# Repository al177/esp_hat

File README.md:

Attributions:
http://github.com/mcuos/kicad-lib - various footprints
https://github.com/StefanHamminga/SH_Antennas.pretty - antenna

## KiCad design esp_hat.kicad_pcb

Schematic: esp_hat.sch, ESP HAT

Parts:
ANT1: ANT_INVERTED_F; TI_DN007_2.4GHz
C1, C2: 10pF; 0603(1608m)-CHIP-CAP
C3: 5.6pF; 0603(1608m)-CHIP-CAP
C4, C5: 0.1uF; 0603(1608m)-CHIP-CAP
C6, C7: 10uF; 0603(1608m)-CHIP-CAP
FB1: FILTER; 0603(1608m)
J1: U.FL; U.FL-COAX
L1, L2: DNP; 0603(1608m)
P1: CONN_02X20; Socket_Strip_Straight_2x20_pi
P2: CONN_01X03; GS3
R1: DNP; 0603(1608m)-CHIP-RESISTOR
R2: 0; 0603(1608m)-CHIP-RESISTOR
R3, R4, R5: DNP; GS2
R6: 12.0K; 0603(1608m)-CHIP-RESISTOR
R7, R8, R9, R10, R11, R12: 200; 0603(1608m)-CHIP-RESISTOR
U1: ESP8266EX; QFN-32-1EP_5x5mm_Pitch0.5mm
U2: AP1117D33; SOT-223-REG_VOUTSLUG
W1: RXD; Measurement_Point_Round-SMD-Pad_Small
W2: TXD; Measurement_Point_Round-SMD-Pad_Small
W3, W4, W5, W6: MOUNT; NPTH_Hole_2_75mm
Y1: 26MHz; crystal_FA238-TSX3225

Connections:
+3V3: C4.1, C5.1, C7.1, U1.1 (VDDA), U1.3 (VDD3P3), U1.4 (VDD3P3), U1.11 (VDDPST), U1.17 (VDDPST), U1.29 (VDDD), U1.30 (VDDA), U2.2 (VO)
+5V: FB1.1, P1.2, P1.4
/5V_filt: C6.1, FB1.2, U2.3 (VI)
/50ohm_LNA: C3.1, L2.1, U1.2 (LNA)
/50ohm_ant: ANT1.2, R2.1
/50ohm_filt: C3.2, L1.1, R1.1, R2.2
/50ohm_ufl: J1.1, R1.2
GND: ANT1.1, C1.2, C2.2, C4.2, C5.2, C6.2, C7.2, J1.2, J1.3, L1.2, L2.2, P1.6, P1.14, P1.20, P1.25, P1.30, P1.34, P1.39, R3.2, R4.2, R5.2, R6.1, U1.33 (GND), U2.1 (GND/ADJ), W3.1, W4.1, W5.1, W6.1
GPIO5: P1.29, P2.1, P2.2, U1.7 (CHIP_EN)
GPIO6: P1.31, P2.3
unnamed: C1.1, U1.27 (XTAL_OUT), Y1.1
unnamed: C2.1, U1.28 (XTAL_IN), Y1.2
unnamed: R3.1, U1.13 (MTDO)
unnamed: R4.1, U1.14 (GPIO2)
unnamed: R5.1, U1.15 (GPIO0)
unnamed: R6.2, U1.31 (RES_12K)
unnamed: R7.2, U1.21 (SD_CLK)
unnamed: R8.2, U1.20 (SD_CMD)
unnamed: R9.2, U1.22 (SD_DATA_0)
unnamed: R10.2, U1.23 (SD_DATA_1)
unnamed: R11.2, U1.18 (SD_DATA_2)
unnamed: R12.2, U1.19 (SD_DATA_3)
unnamed: U1.25 (U0RXD), W1.1
unnamed: U1.26 (U0TXD), W2.1
SD_CLK: P1.15, R7.1
SD_CMD: P1.16, R8.1
SD_D0: P1.18, R9.1
SD_D1: P1.22, R10.1
SD_D2: P1.37, R11.1
SD_D3: P1.13, R12.1

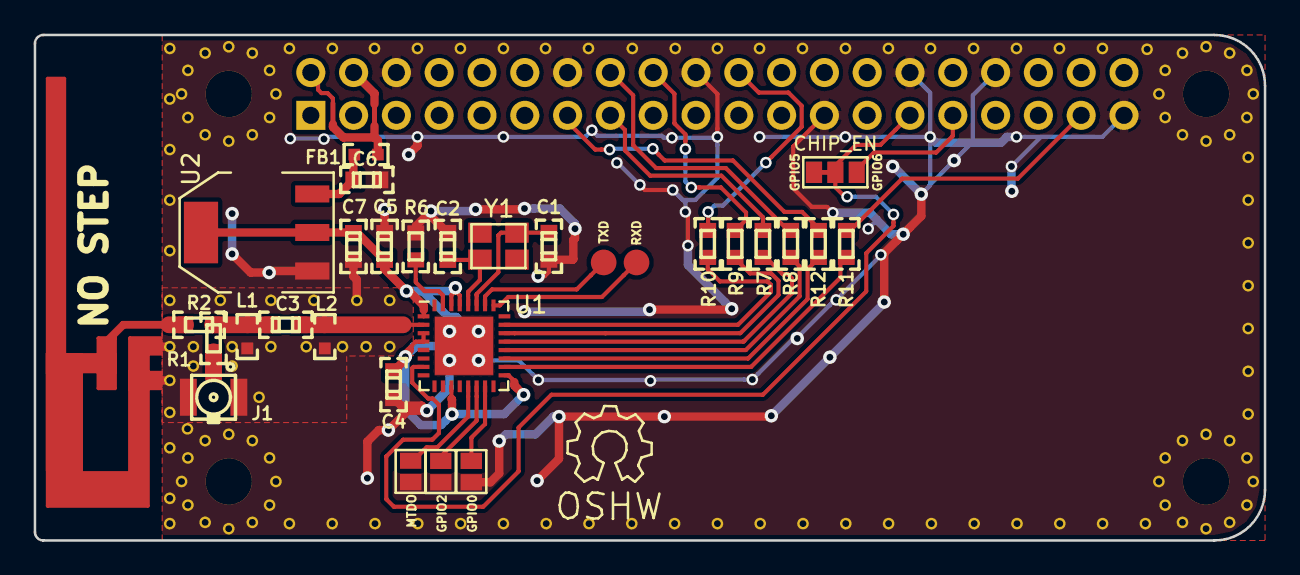
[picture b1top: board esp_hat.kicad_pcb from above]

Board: 2 copper layers, 73.0 x 30.0 mm, 35 parts (1 on the bottom side), 30 nets.

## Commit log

2015-12-11 Initial checkin
2015-12-12 Mostly done
2015-12-12 v0.1 to fab, moved text to back silk, changed license to CC-BY-SA
2015-12-12 Update gerbers with paste file for stencils
2015-12-12 Add PDF of the schematic
2016-01-01 commit v0.2 changes, remove v0.1 fab files
2016-01-01 v0.2 fab files
2016-01-01 Add schematic PDF for v0.2
2016-01-01 Add GPIO5/GPIO6 select pad, fix no-connects, remove paste on option pads
2016-01-01 Change CH_PD name to CHIP_EN
2016-01-04 Add part# parameters, clean up refs, set attributes for proper mfg
